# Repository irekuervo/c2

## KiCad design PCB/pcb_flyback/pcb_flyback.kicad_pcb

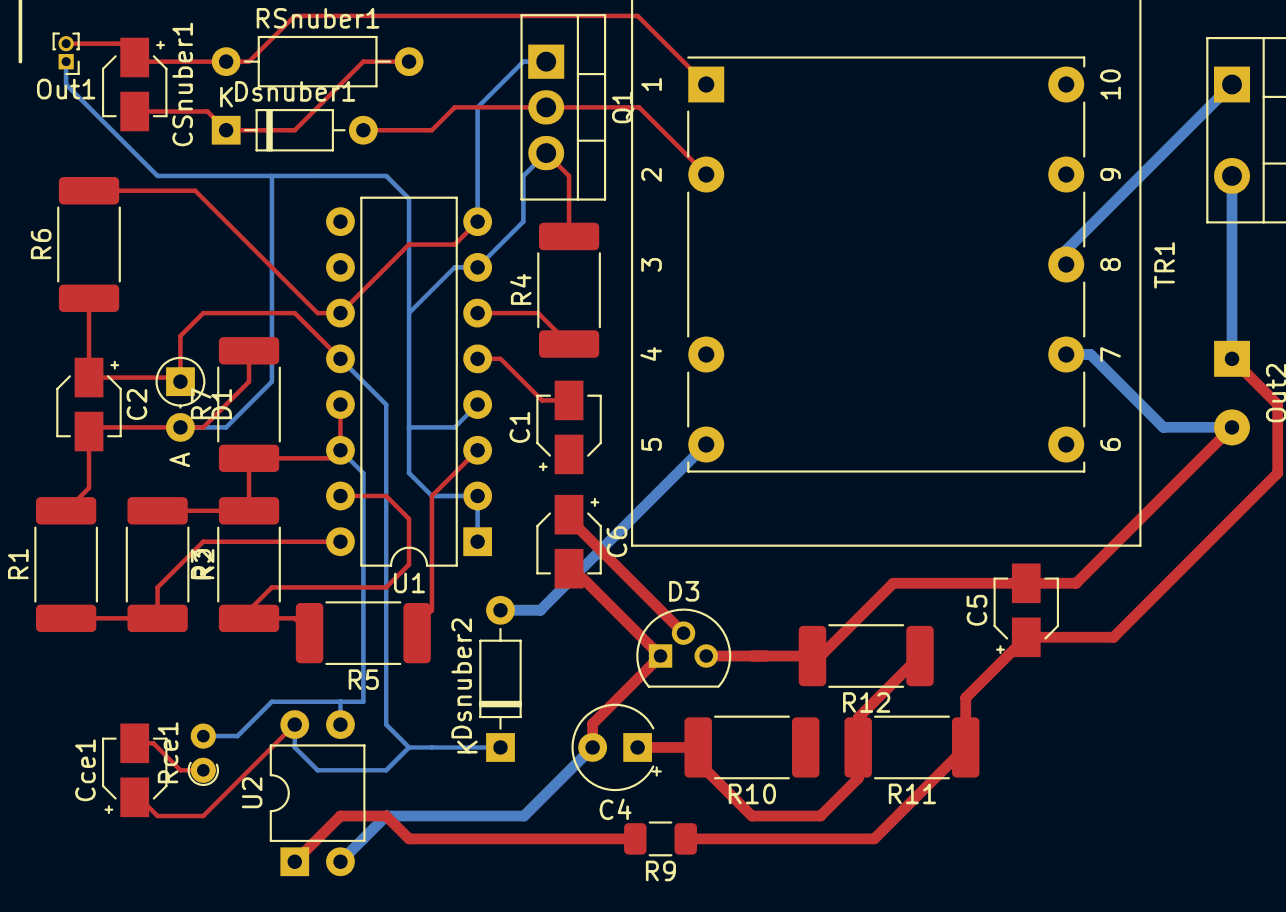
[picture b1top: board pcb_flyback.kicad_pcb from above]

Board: 2 copper layers, 31 parts (0 on the bottom side), 20 nets.

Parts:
C1: 1n; CP_Elec_3x5.3
C2: 22n; CP_Elec_3x5.3
C4: 22n; CP_Radial_Tantal_D4.5mm_P2.50mm
C5: 500u; CP_Elec_3x5.3
C6: 1u; CP_Elec_3x5.3
CSnuber1: 55.2u; CP_Elec_3x5.3
Cce1: 1m; CP_Elec_3x5.3
D1: 15V; D_DO-35_SOD27_P2.54mm_Vertical_AnodeUp
D2: RFU10TF6S; TO-220-2_Vertical
D3: TL431D; TO-92L
Dsnuber1, Dsnuber2: 1N4148; D_DO-35_SOD27_P7.62mm_Horizontal
Out1: Screw_Terminal_01x02; PinHeader_1x02_P1.00mm_Vertical
Out2: Screw_Terminal_01x02; SolderWirePad_1x02_P3.81mm_Drill0.8mm
Q1: IRF540N; TO-220-3_Vertical
R1, R2: 51k; R_2512_6332Metric_Pad1.52x3.35mm_HandSolder
R3: 510; R_2512_6332Metric_Pad1.52x3.35mm_HandSolder
R4, R12: 10k; R_2512_6332Metric_Pad1.52x3.35mm_HandSolder
R5: 5.1k; R_2512_6332Metric_Pad1.52x3.35mm_HandSolder
R6: 150; R_2512_6332Metric_Pad1.52x3.35mm_HandSolder
R7: 860; R_2512_6332Metric_Pad1.52x3.35mm_HandSolder
R9: 4.2k; R_1206_3216Metric
R10: 1m; R_2512_6332Metric_Pad1.52x3.35mm_HandSolder
R11: 38k; R_2512_6332Metric_Pad1.52x3.35mm_HandSolder
RSnuber1: 4k; R_Axial_DIN0207_L6.3mm_D2.5mm_P10.16mm_Horizontal
Rce1: 8k; R_Axial_DIN0204_L3.6mm_D1.6mm_P1.90mm_Vertical
TR1: TRANSF6; Transformer_Breve_TEZ-28x33
U1: TL494; DIP-16_W7.62mm
U2: PC817; DIP-4_W7.62mm

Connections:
GND: C1.1, C2.2, D1.2, Out1.1, Q1.3, R1.2, R4.2, R7.2, TR1.4, U1.1, U1.2, U1.4, U1.7
unnamed: C1.2, U1.5
unnamed: C2.1, Cce1.1, D1.1, Dsnuber2.1, R6.1, U1.12, U2.4
unnamed: C4.1, R10.2, R11.2, R12.1
unnamed: C4.2, C6.2, D3.1, U2.2
unnamed: C5.1, D2.2, Out2.1, R9.1, R11.1
unnamed: C5.2, C6.1, D3.2, D3.3, Out2.2, R12.2, TR1.7
unnamed: CSnuber1.1, Out1.2, RSnuber1.1, TR1.1
unnamed: CSnuber1.2, Dsnuber1.1, RSnuber1.2
unnamed: Cce1.2, Rce1.1
unnamed: D2.1, TR1.8
unnamed: Dsnuber1.2, Q1.2, TR1.2
unnamed: Dsnuber2.2, TR1.3
unnamed: Q1.1, R6.2, U1.8, U1.11
unnamed: R1.1, R2.2, U1.16
unnamed: R2.1, R3.2, R7.1, Rce1.2, U1.13, U1.14, U2.3
unnamed: R3.1, R5.2, U1.15
unnamed: R4.1, U1.6
unnamed: R5.1, U1.3
unnamed: R9.2, U2.1

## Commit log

2021-07-09 Circuito con modelo de Spice TL494 y Nota de aplicacion de TI para flyback converter
2021-07-09 datasheet tl494
2021-07-10 cuentas
2021-07-10 agrego spice del tp
2021-07-10 Circuito previo mail a Fede
2021-07-15 El Tp final queda dentro de la carpeta SPICE y agrego la application note del snuber AN4147
2021-07-15 Red Snubber
2021-07-17 Nota de aplicacion. Diseño de una fuente de switching con TL494
2021-07-18 docu
2021-07-21 pruebas erik
2021-07-22 Agregamos octocoupler (todavia no esta andando del todo)
    Empezamos PCB
2021-07-25 1 Version PCB terminada (Se puede mejorar)
2021-07-25 agrego TL431 a tp y a banco de prueba de optocoupler
2021-07-25 cambio de resistencias de referencia diodo de compensacion
2021-07-26 cambios en PCB
2021-07-27 Pruebas realizadas con Fede, no funciona, se cuelga el LTSpice. Ver que funcione a lazo abierto por un lado, que funcione el opto con el controlador por el otro y cerrar
2021-07-28 Agrego banco de prueba del controlador
2021-07-28 cambios en los bancos de prueba de fuente y controlador
2021-07-28 opto
2021-07-28 clean
2021-07-28 andaaaa
2021-07-28 Cambios PCB, faltan otros
2021-07-28 Cambios PCB
2021-07-28 Se conectó una señal de 12V, 10kHz y 20m de ripple al optocpupler.
    Se conectó el optocoupler con el controlador y la salida del controlador
    controlando el mosfet.
    Hay una señal de salida de 12.9V
    Todavia no se conectó la salida de la fuente con la entrada al opto
2021-07-29 ahi casi te tengo
2021-07-29 ANDA FEITO, PERO ANDA
2021-07-29 ahora si
2021-07-29 a mimir
2021-07-30 PCB 99% listo
2021-07-30 PCB 99,9% listo
2021-08-02 informe
2021-08-02 Cambios en banco de prueba del controlador
2021-08-03 cambio resistencia del snubber
2021-08-04 agrego diodo para limitar potencia
2021-08-05 agrego nuevo snubber, inductancia parasita y driver del mosfet
2021-08-05 carga conmutada
2021-08-06 circuito final con el snubber descalibrado
2021-08-06 imagenes finales
